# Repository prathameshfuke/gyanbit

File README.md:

# 🎮 GyanBit: Code. Play. Build.

<p align="center">

</p>

<p align="center">
  <strong>The First 8-bit Handheld Console Ecosystem for Indian Students.</strong>
</p>

---

## 🚀 What is GyanBit?

GyanBit is an open-source, DIY handheld game console designed for students aged 12–17. It empowers kids to move from **consumers** of technology to **creators** by combining a high-performance browser IDE (GyanBit Studio) with custom RP2040 hardware.

Write your code in **JavaScript** in the browser, test it in our pixel-perfect simulator, and flash it to real hardware with **one click** via WebSerial.

---

## 🤖 Meet BYTE Bot: Your AI Coding Buddy

Integrated directly into GyanBit Studio, **BYTE Bot** is a persistent, AI-powered assistant designed specifically for retro game development.

- **Moveable & Floating**: Draggable window that stays out of your code's way.
- **Smart Knowledge**: Trained on the full `bit.*` API, hardware pin maps, and game logic.
- **Multi-Provider**: Choose between **Groq** (Free & Ultra-Fast) or **Google Gemini**.
- **Privacy First**: All API keys are stored locally in your browser's `localStorage`.

---

## ✨ Features

| Category | Highlights |
|:---|:---|
| 🖥️ **Studio IDE** | React-powered editor, real-time OLED simulator, and dark-theme pixel interface. |
| 🛠️ **Project Flow** | Start fresh with **New Project**, or pick from 7 built-in game templates. |
| ⚡ **One-Click Flash** | Seamless JS → MicroPython translation and USB-C hardware flashing. |
| 🎮 **Built-in Games** | Snake, Pong, Breakout, Dodger, Maze, Flappy Bird, and Space Invaders. |
| 📖 **Tutorials** | Structured 4-part guide to building games from scratch. |
| 🧩 **Hardware** | RP2040 MCU, 1.3" OLED, D-Pad, and Bambo-fiber sustainable shell. |

---

## 📁 Technical Architecture

GyanBit uses a modern, high-performance web stack to deliver a "zero-setup" experience:

```
gyanbit/
├── studio.html          # IDE Entry (React App)
├── chatbot.js           # Self-contained AI Assistant logic
├── src/
│   ├── runtime/         # JavaScript Engine & bit.* API implementation
│   │   ├── MicroPythonGen.js  # JS to MicroPython transpiler 🪄
│   │   └── PixelFont.js       # Fast 5x7 bitmap renderer
│   ├── App.jsx          # IDE UI State Management
│   └── components/      # UI components (Editor, OLED, GamePad, etc.)
└── api/                 # Vercel serverless functions for AI proxying
```

---

## 🚀 Getting Started

### 1. Run Locally
```bash
# Clone the repo
git clone https://github.com/prathameshfuke/gyanbit.git
cd gyanbit

# Install and build
npm install
npm run dev
```
Navigate to `http://localhost:5173` to explore the ecosystem.

### 2. Deployment
GyanBit is optimized for **Vercel**. Simply import the repo, and Vite will be auto-detected for building.
- **Build Command**: `npm run build`
- **Output Dir**: `dist`

---

## 📖 `bit.*` API Reference

The GyanBit runtime provides a high-level API for rapid game development:

| Command | Usage |
|:---|:---|
| `bit.loop(fn)` | The core game loop (runs at ~30 FPS). |
| `bit.clear()` | Wipes the 128x64 display buffer. |
| `bit.text(x, y, str)` | Renders retro-styled text. |
| `bit.fill(x, y, w, h)` | Draws a filled rectangle. |
| `bit.isHeld('up')` | Checks if a button is currently pressed. |
| `bit.beep(hz, ms)` | Triggers a hardware-level square wave beep. |

---

## 🇮🇳 Made in India

Developed with ❤️ by the **Team TC26-GF-005 · MMCOE Pune**.
GyanBit was built to solve the lack of accessible, hands-on CS hardware for Indian rural students.

**License**: [MIT](https://opensource.org/licenses/MIT) © 2026 GyanBit

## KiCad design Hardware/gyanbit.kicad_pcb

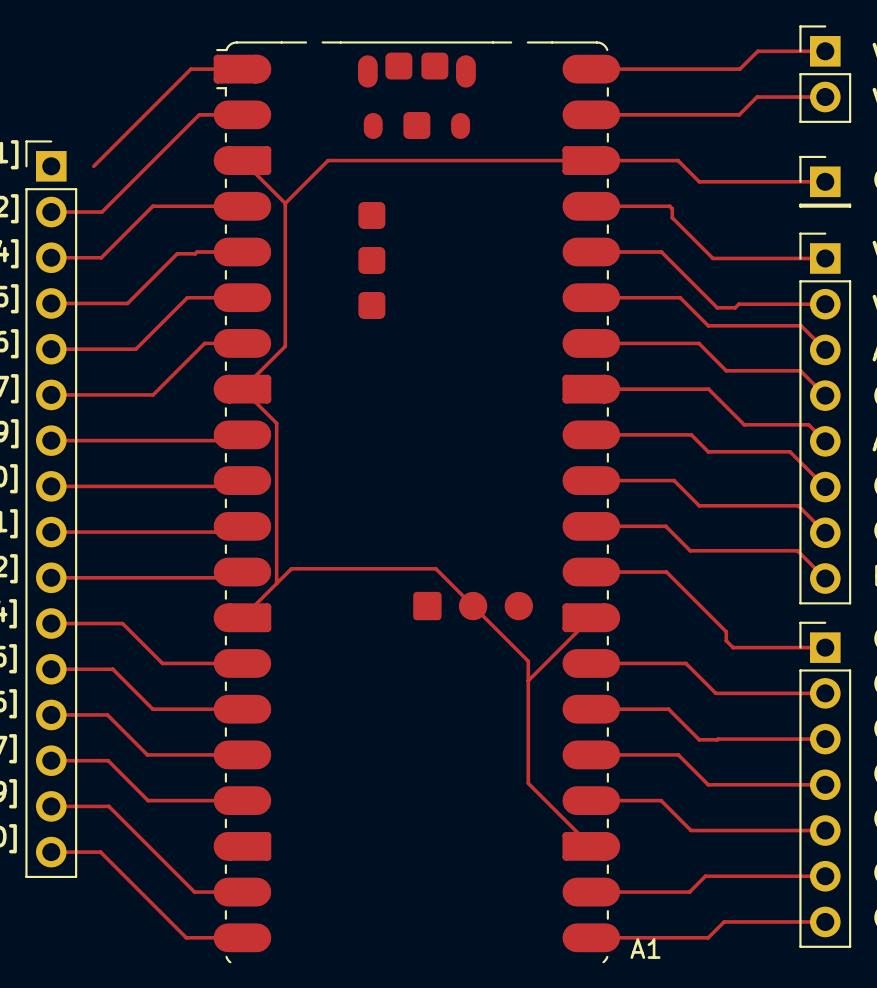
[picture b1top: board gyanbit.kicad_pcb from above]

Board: 2 copper layers, 6 parts (0 on the bottom side), 34 nets.

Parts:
A1: RaspberryPi_Pico_W; RaspberryPi_Pico_W_SMD
J1: Conn_01x16_Socket; PinHeader_1x16_P2.54mm_Vertical
J4: Conn_01x07_Socket; PinHeader_1x07_P2.54mm_Vertical
J5: Conn_01x08_Socket; PinHeader_1x08_P2.54mm_Vertical
J6: Conn_01x02_Socket; PinHeader_1x02_P2.54mm_Vertical
J7: Conn_01x01_Socket; PinHeader_1x01_P2.54mm_Vertical

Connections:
unnamed: A1.36 (3V3), J5.2
unnamed: A1.37 (3V3_EN), J5.1
unnamed: A1.35 (ADC_VREF), J5.3
unnamed: A1.33 (AGND), J5.5
unnamed: A1.1 (GPIO0), J1.1
unnamed: A1.2 (GPIO1), J1.2
unnamed: A1.4 (GPIO2), J1.3
unnamed: A1.5 (GPIO3), J1.4
unnamed: A1.6 (GPIO4), J1.5
unnamed: A1.7 (GPIO5), J1.6
unnamed: A1.9 (GPIO6), J1.7
unnamed: A1.10 (GPIO7), J1.8
unnamed: A1.11 (GPIO8), J1.9
unnamed: A1.12 (GPIO9), J1.10
unnamed: A1.14 (GPIO10), J1.11
unnamed: A1.15 (GPIO11), J1.12
unnamed: A1.16 (GPIO12), J1.13
unnamed: A1.17 (GPIO13), J1.14
unnamed: A1.19 (GPIO14), J1.15
unnamed: A1.20 (GPIO15), J1.16
unnamed: A1.21 (GPIO16), J4.7
unnamed: A1.22 (GPIO17), J4.6
unnamed: A1.24 (GPIO18), J4.5
unnamed: A1.25 (GPIO19), J4.4
unnamed: A1.26 (GPIO20), J4.3
unnamed: A1.27 (GPIO21), J4.2
unnamed: A1.29 (GPIO22), J4.1
unnamed: A1.31 (GPIO26_ADC0), J5.7
unnamed: A1.32 (GPIO27_ADC1), J5.6
unnamed: A1.34 (GPIO28_ADC2), J5.4
unnamed: A1.30 (RUN), J5.8
unnamed: A1.40 (VBUS), J6.1
unnamed: A1.39 (VSYS), J6.2
unnamed: A1.3 (GND), A1.8 (GND), A1.13 (GND), A1.18 (GND), A1.23 (GND), A1.28 (GND), A1.38 (GND), A1.D2 (GND), J7.1

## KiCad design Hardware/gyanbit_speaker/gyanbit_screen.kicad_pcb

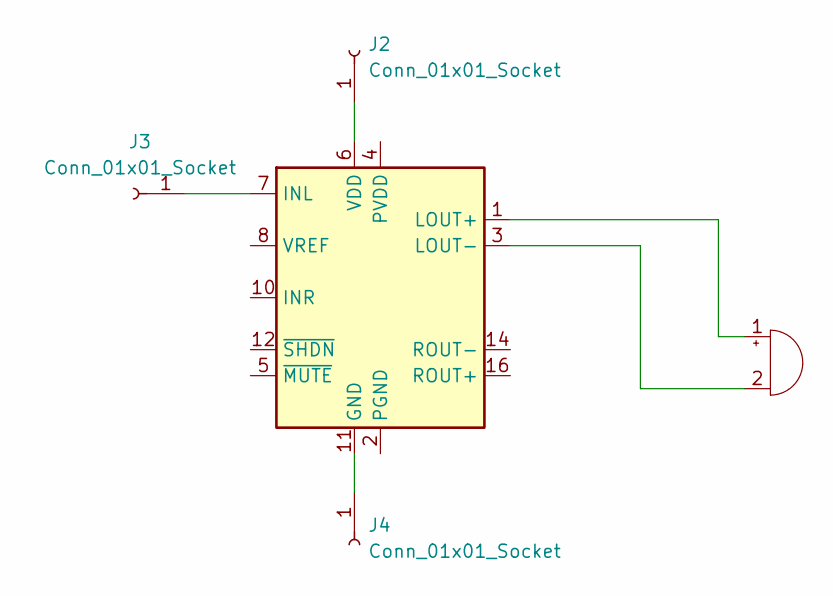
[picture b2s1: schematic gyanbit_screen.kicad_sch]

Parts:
BZ1: Buzzer; MagneticBuzzer_ProSignal_ABI-010-RC
J2, J3, J4: Conn_01x01_Socket; PinHeader_1x01_P2.54mm_Vertical
U1: PAM8403D; SOIC-16_3.9x9.9mm_P1.27mm

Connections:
unnamed: BZ1.1 (+), U1.1 (LOUT+)
unnamed: BZ1.2 (-), U1.3 (LOUT-)
unnamed: J2.1, U1.6 (VDD)
unnamed: J3.1, U1.7 (INL)
unnamed: J4.1, U1.11 (GND)
unnamed: U1.2 (PGND), U1.15 (PGND)
unnamed: U1.4 (PVDD), U1.13 (PVDD)

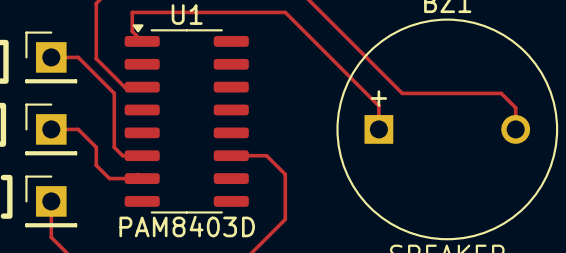
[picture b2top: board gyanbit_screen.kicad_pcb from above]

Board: 2 copper layers, 5 parts (0 on the bottom side), 7 nets.

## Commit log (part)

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2026-03-27 Initial commit for GyanBit console project
2026-03-27 docs: Add Vercel deployment instructions
2026-03-27 refactor: move gyanbit-studio to root for Vercel deployment
2026-03-27 docs: Add logo to README header
2026-03-27 fix(loader): handle document.readyState for Vercel production build
2026-03-27 fix(loader): add robust 1.5s failsafe timeout to prevent production loader freeze
2026-03-27 fix(cache): force hard cache invalidation using aggressive meta headers for Vercel
2026-03-27 fix(loader): final bypass for Vercel race condition using raw inline scripts
2026-03-27 Unify retro-loader hide logic across pages
    Inject a consistent inline loader-hide script into index, about, docs, games, hardware and studio pages to gracefully fade and remove #retro-loader (uses double requestAnimationFrame + timeouts and a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
2026-03-27 Use module script and convert studio buttons
    Change script includes to use ES module loading (type="module" src="/script.js") across index.html, about.html, docs.html, games.html, and hardware.html. Replace JavaScript-triggered "Open Studio" bu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
2026-03-27 Final Refactor
    BYTE Bot: AI assistant is now a draggable floating window, exclusive to the Studio IDE with dual Groq/Gemini support.
    IDE Fixes: Restored standard shortcuts (Undo, Copy, Select All) and added "New Project" triggers to the toolbar and gallery.
    UI/UX: Implemented a premium "floating" interface with rounded corners, neon accents, and deep shadows for a modern retro look.
    Docs: Overhauled the root README.md with professional branding, technical architecture, and a one-click Vercel setup guide.
2026-03-28 feat: multi-provider BYTE Bot, draggable UI, and IDE shortcut fixes
2026-03-28 fix: set Node.js engine to 24.x for Vercel deployment
2026-03-28 fix: remove engines field, let Vercel use default Node.js
2026-03-28 fix: set Node.js engine to 20.x for Vercel
2026-03-28 fix: remove pinned @vercel/node runtime and engines field to resolve Node version conflict
2026-03-28 Add Hardware KiCad projects and fp-info-cache
    Import gyanbit KiCad hardware files and related assets: gyanbit.kicad_pcb, .kicad_sch, .kicad_pro, .kicad_prl, speaker variant files, and multiple timestamped backup ZIPs. Also add a large fp-info-ca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
2026-04-10 Integrate JS-DOS Ultimate DOOM with custom keyboard mappings
2026-04-11 feat: add studio arcade menu and racing games
2026-04-11 chore: include remaining local files for full sync
2026-04-11 chore: remove .claude files
2026-04-11 fix: F1 and racing constraints, game layers docs, snake/arcade menu bounds, restore legacy games
